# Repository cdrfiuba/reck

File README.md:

# reck
R.E.C.K

Robot Eyes Caterpillar Kinect

Robot autónomo con capacidad para filmar, seguir un objeto, entre otras caracteristicas.

Caracteristicas generales: altura entre 1 y 1,5 metros; sistema de desplazamiento con orugas; cuenta con una Raspberry Pi; "cabeza" formada por una Kinect; "cuerpo" acoplado a la estructura de un gabinete, lugar donde se van a colocar las placas de conexión; la estructura va a estar conectada a través de caños; la proteccion de las placas va a ser con placa de acrílilco.

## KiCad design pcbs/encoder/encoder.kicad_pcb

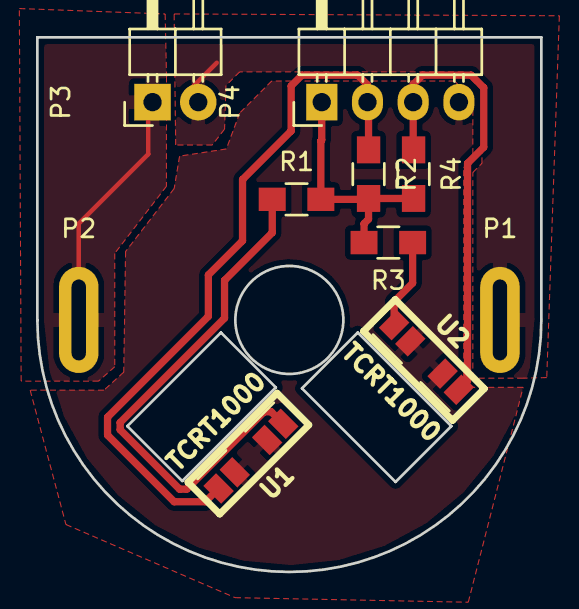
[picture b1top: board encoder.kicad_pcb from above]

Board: 2 copper layers, 28.0 x 29.7 mm, 10 parts (0 on the bottom side), 8 nets.

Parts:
P1: M1; SolderWirePad_single_2-5mmDrill
P2: M2; SolderWirePad_single_2-5mmDrill
P3: Motor; Pin_Header_Angled_1x02
P4: CONN_01X04; Pin_Header_Angled_1x04
R1, R2: 180; R_0805_HandSoldering
R3, R4: 33k; R_0805_HandSoldering
U1: TCRT1000; tcrt1000-smd
U2: TCRT1000

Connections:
+5V: P4.1, R1.2, R2.2, R3.2, R4.2
/S1: P4.2, R2.1, U1.4
/S2: P4.3, R4.1, U2.4
GND: P4.4, U1.2, U1.3, U2.2, U2.3
unnamed: P1.1, P3.2
unnamed: P2.1, P3.1
unnamed: R1.1, U1.1
unnamed: R3.1, U2.1

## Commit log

2016-08-13 Plantilla para las maderas
    Plantilla para poder marcar los agujeros de las maderas para las orugas
2016-09-30 encoder a utilizar en el motor
2016-09-30 PCB del encoder
2017-03-04 muevo la plantilla a la carpeta 3d y actualizo
2017-03-04 actualizo giignore
2017-10-07 agregamos una pieza para sostener las barras M8
2017-10-20 correccion en el diamentro de la barra
2017-10-20 agrego los engranajes
2017-10-21 actualizacion de engranajes para reck
2017-10-23 Agregue las dos tapas de engranajes
2017-10-27 agrego *.stl al gitignore
2017-10-29 actualizacion de engranajes para reck con tapa abierta y cerrada
2017-11-11 agrego el esquema de todos los engranajes de una oruga
2017-11-11 corregimos medidas para canio de 1 1/2
2017-11-21 cambios hechos a partir de la primera impresion
2017-12-02 Agregamos un tope al soporte de buje
